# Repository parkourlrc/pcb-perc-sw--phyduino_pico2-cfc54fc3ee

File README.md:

# Phyduino Pico 2

An Arduino Uno-style development board built around the Raspberry Pi **RP2350** microcontroller, designed by the University of Toronto Department of Physics, Electronics Support Services, for the [Introduction to Electronics](https://perc-sw.github.io/intro_to_electronics/) course. Students assemble part of the board themselves, learning surface-mount soldering, microcontroller programming, analogue-to-digital conversion and digital communication.

**Project site:** <https://perc-sw.github.io/phyduino_pico2> (schematic, interactive BOM, PCB drawings, 3D model and datasheets)

> **Status:** Rev A0 prototype (October 2026).

## Features

### Microcontroller and memory
- **RP2350B** (QFN-80): dual Arm Cortex-M33 or Hazard3 RISC-V cores, 12 MHz crystal
- **16 MB** QSPI NOR flash (AT25QF128A)
- **8 MB** QSPI PSRAM (IS66WVS8M8FBLL)
- **8 KB** I²C EEPROM (AT24C64D)

### Analogue inputs
- Six analogue inputs (**A0–A5**) measured by an 8-channel, **12-bit SAR ADC** (ADS7038) on SPI
- The ADC runs from a dedicated 5 V analogue supply, with an **AREF** pin on the header
- The board's input voltage is monitored by one of the RP2350's own ADC inputs

### Wireless
- **ESP32-C6-MINI-1** module: 2.4 GHz Wi-Fi 6 and Bluetooth 5 (LE). The pin-compatible ESP32-C61-MINI-1 can be fitted instead.
- Runs [ESP-AT](https://github.com/perc-sw/esp-at) firmware as a network co-processor, connected to the RP2350 over UART with RTS/CTS flow control
- The RP2350 controls the module's enable and boot pins, and a separate UART is provided for loading the module's firmware

### Connectors and I/O
- **Arduino Uno R3 form factor** (68.6 × 53.3 mm) with standard headers: D0–D15, A0–A5, AREF, IOREF, RESET, 3.3 V, 5 V and V<sub>IN</sub>
- **USB-C:** USB 2.0 and 5 V power, with ESD protection
- **Qwiic / STEMMA QT** connector (I²C on D14/D15, 3.3 V)
- **HSTX connector** (22-pin, 0.5 mm FFC): the RP2350's four high-speed differential HSTX lanes, plus I²C and two GPIO
- **SWD debug connector** (3-pin JST-SH, Raspberry Pi debug probe pinout)
- **I²C GPIO expander** (FXL6408) for power-path status and control

### Power
- Two inputs:
  - **USB-C:** 4.5–5.5 V, up to 3 A
  - **DC barrel jack** (2.1 mm): 4.5–22 V, up to 3 A
- Each input has a **TPS25947 eFuse** with over-voltage, under-voltage and reverse-current protection and current limiting (2.6 A)
- **AP63301** synchronous buck regulators (3 A) generate the 3.3 V and 5 V rails
- A **TPS2121** power mux supplies the 5 V rail:
  - from the 5 V regulator when the input is above 5.5 V
  - directly from the input otherwise, for example on USB power

### Reset and boot
- One **RESET/BOOT** button, handled by a TPS3424 push-button controller:
  - **Short press:** reset and run the program in flash
  - **Long press (about 2 s):** restart in **UF2 (BOOTSEL) mode**, where the board appears as a USB drive for drag-and-drop programming

## Repository layout

| Path | Contents |
|---|---|
| `phyduino_pico2.kicad_pro` | KiCad project (net classes, design rules, DRC exclusions) |
| `phyduino_pico2.kicad_sch` | Root schematic: headers and connectors, with the Microcontroller, Power and Wireless Communication sub-sheets |
| `phyduino_pico2_mcu.kicad_sch` | Microcontroller: RP2350, crystal and debug connector, with two sub-sheets |
| `phyduino_pico_memory.kicad_sch` | Memory: QSPI flash, PSRAM and the RESET/BOOT button controller |
| `phyduino_pico_peripherals.kicad_sch` | Peripherals: ADC, EEPROM and I²C GPIO expander |
| `phyduino2_power_regs.kicad_sch` | Power: eFuses, power mux and buck regulators |
| `phyduino_pico2_wifi.kicad_sch` | Wireless Communication: ESP32-C6 module |
| `phyduino_pico2.kicad_pcb` | 4-layer PCB |
| `scripts/` | Pre-release check: documentation links, generated outputs, part numbers and pinout against the design |
| `ibom.config.ini` | Settings for the student interactive BOM (InteractiveHtmlBom plugin) |
| `fabrication/` | Gerber and drill files |
| `docs/` | [Project site](https://perc-sw.github.io/phyduino_pico2): schematic and PCB PDFs, interactive BOMs, 3D models, datasheets and design reviews |

## Opening the design

The design files are in **KiCad 10** format and can't be opened with earlier versions.

Some symbols and footprints come from the maintainer's own libraries, which aren't in this repository. KiCad may report these as missing library links. The board and schematic still open and plot correctly, because every footprint and symbol is stored in the design files.

The board's silkscreen and copper text use Liberation Sans, Tekton, Centaur and Photograph Signature. Install the fonts in [`.github/workflows/fonts/`](.github/workflows/fonts/) so the text renders as it does on the fabricated board.

## Related projects

- [Phyduino Pico](https://perc-sw.github.io/phyduino_pico/): the previous RP2040 board
- [Analog Shield](https://perc-sw.github.io/analog_shield)
- [Analog Shield 2](https://github.com/perc-sw/analog_shield2)
- [Phyduino Board Support](https://perc-sw.github.io/phyduino_bsp/) 

## Licence

Released under the GNU General Public License v3.0. See [LICENSE](LICENSE).

University of Toronto, Department of Physics: [Electronics Support Services](https://www.physics.utoronto.ca/physics-at-uoft/services/plrs/electronic-support-services/)

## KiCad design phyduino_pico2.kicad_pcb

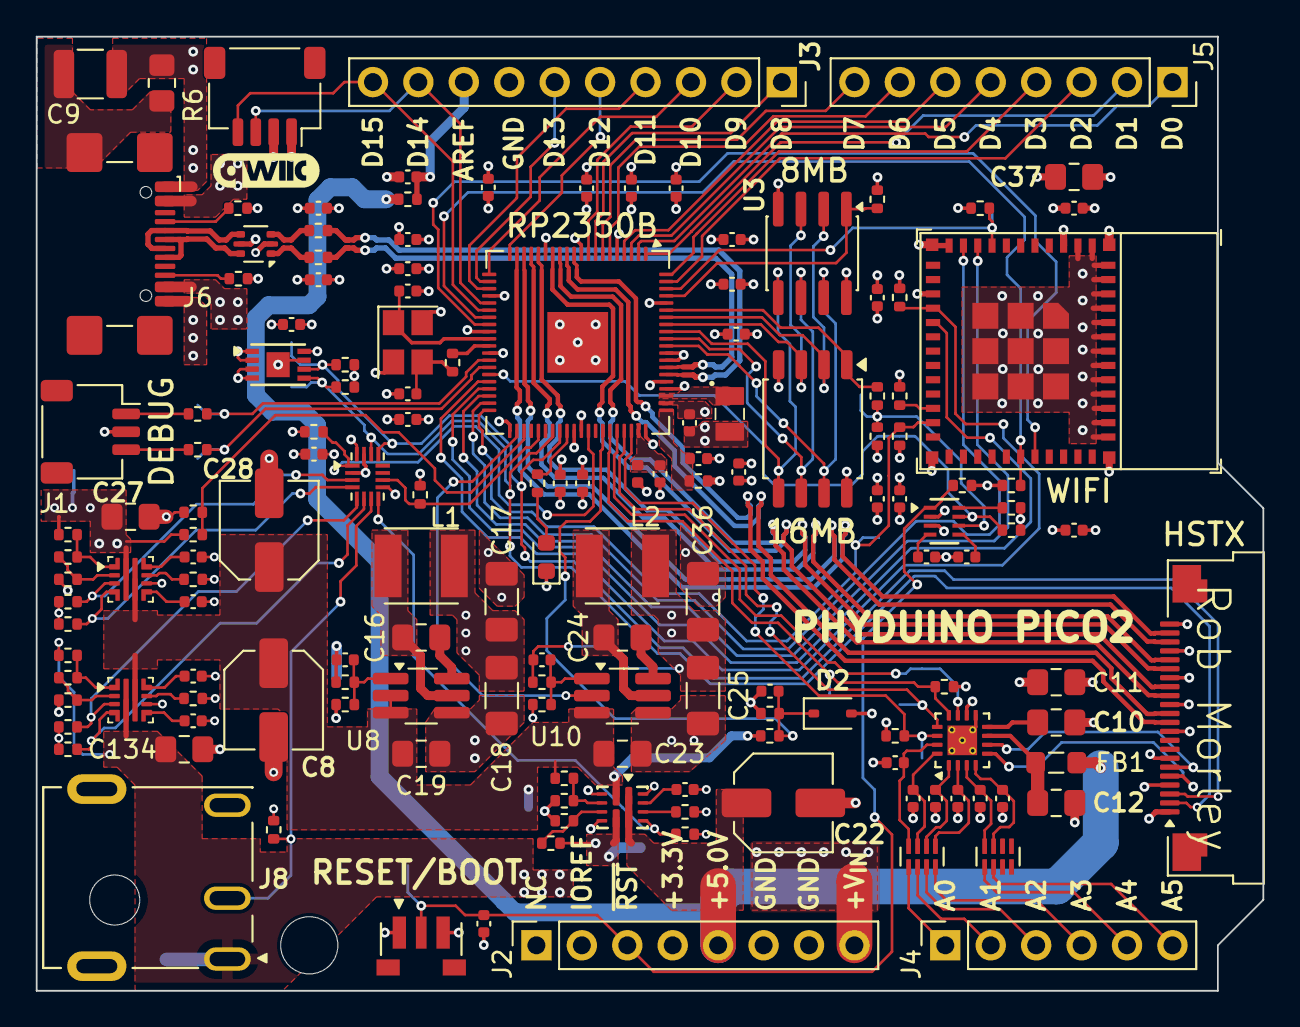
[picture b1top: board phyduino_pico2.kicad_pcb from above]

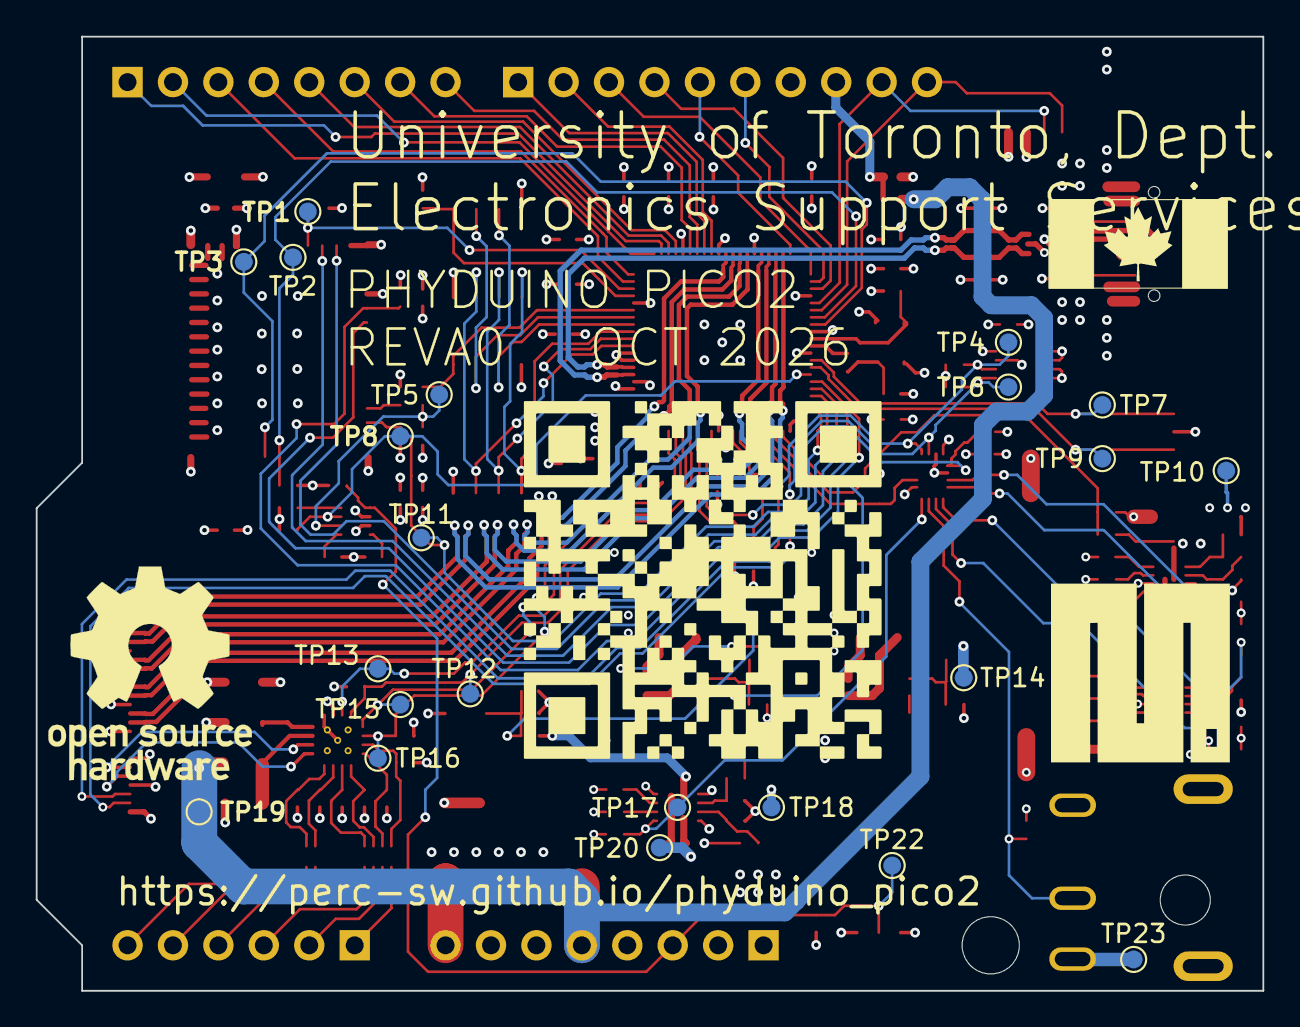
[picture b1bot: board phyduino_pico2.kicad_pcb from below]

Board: 4 copper layers, 68.6 x 53.3 mm, 175 parts (22 on the bottom side), 129 nets.

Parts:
C1, C6, C13, C20, C21, C26, C29, C34, C57, C110, C111, C117, C119, C125, C126, C127, C128, C129, C130, C131, C132, C133, C135, C137, C139: 0.1µF; C_0402_1005Metric
C2, C3, C4, C120: 4.7µF; C_0402_1005Metric
C5, C7: 100pF; C_0402_1005Metric
C8, C22, C28: 100µF; C_Elec_5x5.4
C9: 0.1µF; C_1210_3225Metric
C10, C11, C12, C134: 1µF; C_0805_2012Metric_Pad1.18x1.45mm_HandSolder
C14, C15: 27pF; C_0402_1005Metric
C16, C24: 0.1µF; C_0805_2012Metric_Pad1.18x1.45mm_HandSolder
C17, C18, C25, C36: 22µF; C_1206_3216Metric_Pad1.33x1.80mm_HandSolder
C19, C23, C27, C37: 10µF; C_0805_2012Metric_Pad1.18x1.45mm_HandSolder
C30, C31, C32, C33, C35, C38, C59: 1000pF; C_0402_1005Metric
C39: 1µF; C_0402_1005Metric
C58: 4700pF; C_0402_1005Metric
C136, C141: 1nF; C_0402_1005Metric
C140: 3300pF; C_0402_1005Metric
D1: GREEN; LED_0603_1608Metric
D2: 3.6V; D_SOD-323
FB1: 1kΩ@100MHz; L_0805_2012Metric_Pad1.05x1.20mm_HandSolder
FB100: MPZ1005S221HT000; L_0402_1005Metric
H2: MountingHole; MountingHole_3.2mm_M3
J1: SM03B-SRSS-TB; JST_SH_SM03B-SRSS-TB_1x03-1MP_P1.00mm_Horizontal
J2, J5: PPPC081LFBN-RC; PinSocket_1x08_P2.54mm_Vertical
J3: PPPC101LFBN-RC; PinSocket_1x10_P2.54mm_Vertical
J4: PPPC061LFBN-RC; PinSocket_1x06_P2.54mm_Vertical
J6: USB4110-GF-A; GCT-USBC-GCT_USB4110
J7: F32Q-1A7H1-11022; Amphenol_F32Q-1A7x1-11022_1x22-1MP_P0.5mm_Horizontal
J8: 54-00127; TENSILITY_54-00127
J9: SM04B-SRSS-TB; JST_SH_SM04B-SRSS-TB_1x04-1MP_P1.00mm_Horizontal
L1: 6.8µH; L_Bourns_SRP4021HMCT
L2: 10µH; L_Bourns_SRP4021HMCT
L3: 3.3µH; L_Abracon_AOTA-B201610S
R1, R2: 100Ω; R_0402_1005Metric
R3, R4, R5: 27Ω; R_0402_1005Metric
R6: 220kΩ; R_0805_2012Metric_Pad1.20x1.40mm_HandSolder
R13: 620Ω; R_0402_1005Metric
R20, R21, R22, R44, R45, R49, R51, R52, R53, R63, R64, R136, R137, R153, R157, R158, R162, R163, R164, R166: 10kΩ; R_0402_1005Metric
R42, R43, R47, R48, R50, R55, R61, R62, R65: 5.1kΩ; R_0402_1005Metric
R46, R139, R156: 1.1kΩ; R_0402_1005Metric
R56: 196kΩ; R_0402_1005Metric
R57: 62kΩ; R_0402_1005Metric
R58: 158kΩ; R_0402_1005Metric
R59: 30kΩ; R_0402_1005Metric
R134, R135, R138: 42.2kΩ; R_0402_1005Metric
R143, R149: 732kΩ; R_0402_1005Metric
R146, R155: 215kΩ; R_0402_1005Metric
R150, R154: 53.6kΩ; R_0402_1005Metric
R151: 22kΩ; R_0402_1005Metric
R152: 33kΩ; R_0402_1005Metric
R165: 100kΩ; R_0402_1005Metric
RN1, RN2: 1.0kΩ; RESCAV50P200X100X55-8N
SW1: 1977067-1; TE_1977067-1
TP1, TP2, TP3, TP4, TP5, TP6, TP7, TP8, TP9, TP10, TP11, TP12, TP13, TP14, TP15, TP16, TP17, TP18, TP19, TP20, TP22, TP23: TestPoint_Small; TestPoint_SameSky_CPG-47-TH-B
U1: RP2350B; QFN-80-1EP_10x10mm_P0.4mm_EP3.4x3.4mm
U2: AT25QF128A-SHB-T; SOIC-8_5.3x5.3mm_P1.27mm
U3: IS66WVS8M8FBLL-104NLI; SOIC-8_3.9x4.9mm_P1.27mm
U5: ADS7038IRTER; QFN50P300X300X80-17N
U6, U13: TPS259470ARPWR; Texas_Instruments_VQFN-HR-10
U7: AT24C64D-MAHM-T; DFN-8-1EP_3x2mm_P0.5mm_EP1.3x1.4mm
U8, U10: AP63301WU-7; TSOT-23-6_HandSoldering
U9: USBLC6-2P6; SOT-666
U11: ESP32-C6-MINI-1-H4; ESP32-C6-MINI-1
U14: FXL6408UMX; QFN40P260X180X55-16N
U15: TPS3424C11EF2ADRLR; SOT-5x3_DRL0008A_TEX
U108: TPS2121RUXR; VQFN-HR-12
Y1: ABM8G-12.000MHZ-18-D2Y-T; Crystal_SMD_Abracon_ABM8AIG-4Pin_3.2x2.5mm

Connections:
+1.1V: C2.1, C119.1, C120.1, C135.1, L3.1, U1.10 (DVDD), U1.32 (DVDD), U1.51 (DVDD), U1.65 (VREG_FB)
+3.3V: C1.1, C3.1, C5.1, C6.1, C11.1, C13.1, C17.1, C18.1, C20.1, C21.1, C26.1, C29.1, C34.1, C37.2, C110.1, C111.1, C125.1, C126.1, C127.1, C128.1, C129.1, C130.1, C133.1, C137.1, FB100.1, J2.2, J2.4, J7.1, J9.2, L1.2, R5.1, R20.1, R21.1, R22.1, R42.1, R43.1, R44.1, R45.1, R50.1, R51.1, R52.2, R55.1, R56.1, R61.1, R62.1, R63.1, R64.1, R153.2, R157.2, R158.2, R162.2, R163.2, R164.2, TP14.1 (1_1), U1.5 (IOVDD), U1.15 (IOVDD), U1.24 (IOVDD), U1.29 (IOVDD), U1.41 (IOVDD), U1.50 (IOVDD), U1.60 (IOVDD), U1.64 (VREG_VIN), U1.68 (USB_OTP_VDD), U1.69 (QSPI_IOVDD), U1.76 (IOVDD), U2.8 (VCC), U3.8 (VDD), U5.10 (DVDD), U7.8 (VCC), U9.5 (VBUS), U11.3 (3V3), U14.2 (VDDIO), U14.15 (VCC), U15.3 (VDD)
+3.3VA: C117.1, FB100.2, U1.59 (ADC_AVDD)
+5.0V: C22.1, FB1.1, J2.5, R65.1, TP19.1 (1_1), U108.1 (OUT), U108.8 (OUT)
+5.0VA: C12.1, FB1.2, U5.7 (AVDD)
+5.0V_DCDC: C7.1, C25.1, C36.1, L2.2, R58.1, R135.2, TP20.1 (1_1), U108.7 (IN1)
+VIN_REG: C8.1, C19.1, C23.1, C28.1, R138.2, R165.2, TP18.1 (1_1), U6.6 (OUT), U8.2 (EN), U8.3 (IN), U10.3 (IN), U13.6 (OUT), U108.2 (IN2)
+V_{EXTERNAL}: C134.1, J2.8, J8.1, R143.2, TP23.1 (1_1), U6.5 (IN)
+V_{USB}: C27.1, J6.A4 (VBUS), J6.A9 (VBUS), J6.B4 (VBUS), J6.B9 (VBUS), R149.2, R151.2, TP10.1 (1_1), U13.5 (IN)
/AREF: C39.1, J3.8, R65.2
/Microcontroller/A0: J4.1, RN1.1 (R1.1)
/Microcontroller/A1: J4.2, RN1.2 (R2.1)
/Microcontroller/A2: J4.3, RN1.3 (R3.1)
/Microcontroller/A3: J4.4, RN1.4 (R4.1)
/Microcontroller/A4: J4.5, RN2.1 (R1.1)
/Microcontroller/A5: J4.6, RN2.2 (R2.1)
/Microcontroller/ADC_MISO: R43.2, TP12.1 (1_1), U1.55 (GPIO44), U5.12 (SDO)
/Microcontroller/ADC_MOSI: R42.2, TP16.1 (1_1), U1.58 (GPIO47), U5.14 (SDI)
/Microcontroller/ADC_SCK: TP15.1 (1_1), U1.57 (GPIO46), U5.13 (SCLK)
/Microcontroller/ADC_nCS: TP13.1 (1_1), U1.56 (GPIO45), U5.11 (~CS)
/Microcontroller/BUILTIN_LED: R46.1, U1.49 (GPIO40)
/Microcontroller/D0: J5.1, U1.2 (GPIO5)
/Microcontroller/D1: J5.2, U1.1 (GPIO4)
/Microcontroller/D2: J5.3, U1.79 (GPIO2)
/Microcontroller/D3: J5.4, U1.80 (GPIO3)
/Microcontroller/D4: J5.5, U1.3 (GPIO6)
/Microcontroller/D5: J5.6, U1.4 (GPIO7)
/Microcontroller/D6: J5.7, U1.6 (GPIO8)
/Microcontroller/D7: J5.8, U1.7 (GPIO9)
/Microcontroller/D8: J3.1, U1.8 (GPIO10)
/Microcontroller/D9: J3.2, U1.9 (GPIO11)
/Microcontroller/D10: J3.3, U1.21 (GPIO21)
/Microcontroller/D11: J3.4, U1.23 (GPIO23)
/Microcontroller/D12: J3.5, U1.20 (GPIO20)
/Microcontroller/D13: J3.6, U1.22 (GPIO22)
/Microcontroller/D14: J3.9, J9.3, U1.25 (GPIO24)
/Microcontroller/D15: J3.10, J9.4, U1.26 (GPIO25)
/Microcontroller/DBIO_SWCLK: R1.2, TP7.1 (1_1), U1.33 (SWCLK)
/Microcontroller/DBIO_SWDIO: R2.2, TP9.1 (1_1), U1.34 (SWDIO)
/Microcontroller/DEBUG_SWCLK: J1.1, R1.1
/Microcontroller/DEBUG_SWDIO: J1.3, R2.1
/Microcontroller/EN_5V: U1.42 (GPIO33), U10.2 (EN)
/Microcontroller/EXT_AUXOFF: R158.1, U6.3 (AUXOFF), U14.5 (GPIO5)
/Microcontroller/EXT_~FLT: R157.1, U6.4 (~FLT), U14.6 (GPIO4)
/Microcontroller/EXT_~RESET: C57.1, J2.3, R22.2, SW1.2, TP22.1 (1_1), U15.1 (PB)
/Microcontroller/FLASH_CLK: U1.71 (QSPI_SCK), U2.6 (SCK), U3.6 (CLK)
/Microcontroller/FLASH_SD0: U1.72 (QSPI_SD0), U2.5 (I/O_{0}), U3.5 (SIO0)
/Microcontroller/FLASH_SD1: U1.74 (QSPI_SD1), U2.2 (I/O_{1}), U3.2 (SIO1)
/Microcontroller/FLASH_SD2: U1.73 (QSPI_SD2), U2.3 (IO_{2}), U3.3 (SIO2)
/Microcontroller/FLASH_SD3: U1.70 (QSPI_SD3), U2.7 (I/O_{3}), U3.7 (SIO3)
/Microcontroller/FLASH_~CS: R49.1, U1.75 (QSPI_~CS), U2.1 (~CS)
/Microcontroller/HSTX_LANE0_N: J7.12, U1.12 (GPIO13)
/Microcontroller/HSTX_LANE0_P: J7.11, U1.11 (GPIO12)
/Microcontroller/HSTX_LANE1_N: J7.15, U1.14 (GPIO15)
/Microcontroller/HSTX_LANE1_P: J7.14, U1.13 (GPIO14)
/Microcontroller/HSTX_LANE2_N: J7.18, U1.17 (GPIO17)
/Microcontroller/HSTX_LANE2_P: J7.17, U1.16 (GPIO16)
/Microcontroller/HSTX_LANE3_N: J7.21, U1.19 (GPIO19)
/Microcontroller/HSTX_LANE3_P: J7.20, U1.18 (GPIO18)
/Microcontroller/HS_GPIO0: J7.5, U5.5 (AIN6/GPIO6)
/Microcontroller/HS_GPIO1: J7.6, U5.6 (AIN7/GPIO7)
/Microcontroller/I2C1_SCL: J7.3, R62.2, TP4.1 (1_1), U1.48 (GPIO39), U7.6 (SCL), U14.13 (SCL)
/Microcontroller/I2C1_SDA: J7.2, R61.2, TP6.1 (1_1), U1.47 (GPIO38), U7.5 (SDA), U14.14 (SDA)
/Microcontroller/IO_EXP_~INT: R63.2, U1.52 (GPIO41), U14.1 (~INT)
/Microcontroller/IO_EXP_~RST: R64.2, U1.45 (GPIO36), U14.10 (~RST)
/Microcontroller/MCU_VREG_AVDD: C4.1, R5.2, U1.61 (VREG_AVDD)
/Microcontroller/MCU_VREG_LX: L3.2, U1.63 (VREG_LX)
/Microcontroller/MCU_XIN: C14.1, U1.30 (XIN), Y1.1
/Microcontroller/MCU_XOUT: R13.2, U1.31 (XOUT)
/Microcontroller/Memory/BOOT_LP_CAP: C58.1, U15.5 (LPT)
/Microcontroller/Memory/MCU_BOOT_SEL: R49.2, R52.1, TP5.1 (1_1), U15.6 (~RESET)
/Microcontroller/Memory/RESET_SP_CAP: C59.1, U15.4 (SPT)
/Microcontroller/PSW_STATUS: R153.1, TP17.1 (1_1), U14.8 (GPIO2), U108.9 (ST)
/Microcontroller/Peripherals/AIN0: C30.1, RN1.8 (R1.2), U5.15 (AIN0/GPIO0)
/Microcontroller/Peripherals/AIN1: C31.1, RN1.7 (R2.2), U5.16 (AIN1/GPIO1)
/Microcontroller/Peripherals/AIN2: C32.1, RN1.6 (R3.2), U5.1 (AIN2/GPIO2)
/Microcontroller/Peripherals/AIN3: C33.1, RN1.5 (R4.2), U5.2 (AIN3/GPIO3)
/Microcontroller/Peripherals/AIN4: C35.1, RN2.8 (R1.2), U5.3 (AIN4/GPIO4)
/Microcontroller/Peripherals/AIN5: C38.1, RN2.7 (R2.2), U5.4 (AIN5/GPIO5)
/Microcontroller/SYS_nRST: R20.2, TP8.1 (1_1), U1.35 (RUN), U15.7 (~INT)
/Microcontroller/USB_AUXOFF: R163.1, U13.3 (AUXOFF), U14.3 (GPIO7)
/Microcontroller/USB_D_N: R3.1, U9.3 (I/O2)
/Microcontroller/USB_D_P: R4.1, U9.1 (I/O1)
/Microcontroller/USB_IO_D_N: R3.2, U1.66 (USB_DM)
/Microcontroller/USB_IO_D_P: R4.2, U1.67 (USB_DP)
/Microcontroller/USB_~FLT: R162.1, U13.4 (~FLT), U14.4 (GPIO6)
/Microcontroller/VBUS_DETECT: R151.1, R152.2, U1.43 (GPIO34)
/Microcontroller/VIN_MONITOR: C141.1, D2.1 (K), R165.1, R166.2, U1.54 (GPIO43)
/Microcontroller/WIFI_BOOT1: R44.2, TP11.1 (1_1), U1.40 (GPIO32), U11.23 (IO9)
/Microcontroller/WIFI_DL_UART_RX: TP3.1 (1_1), U1.28 (GPIO27), U11.31 (TXD0)
/Microcontroller/WIFI_DL_UART_TX: R50.2, TP2.1 (1_1), U1.27 (GPIO26), U11.30 (RXD0)
/Microcontroller/WIFI_ENA: R53.1, TP1.1 (1_1), U1.78 (GPIO1), U11.8 (EN)
/Microcontroller/WIFI_UART_CTS: U1.38 (GPIO30), U11.9 (IO4)
/Microcontroller/WIFI_UART_RTS: U1.39 (GPIO31), U11.10 (IO5)
/Microcontroller/WIFI_UART_RX: U1.37 (GPIO29), U11.16 (IO7)
/Microcontroller/WIFI_UART_TX: R55.2, U1.36 (GPIO28), U11.15 (IO6)
/Microcontroller/XOUT: C15.1, R13.1, Y1.3
/Microcontroller/~EXT_PWR: J8.3, R164.1, U14.7 (GPIO3)
/Power/DCDC_3V3_BST: C16.1, U8.6 (BST)
/Power/DCDC_3V3_FB: C5.2, R56.2, R57.1, U8.1 (FB)
/Power/DCDC_3V3_SW: C16.2, L1.1, U8.5 (SW)
/Power/DCDC_5V0_BST: C24.1, U10.6 (BST)
/Power/DCDC_5V0_FB: C7.2, R58.2, R59.1, U10.1 (FB)
/Power/DCDC_5V0_SW: C24.2, L2.1, U10.5 (SW)
/Power/EXT_ILIM: R139.2, U6.9 (ILM)
/Power/EXT_ITIMER: C132.1, U6.10 (ITIMER)
/Power/EXT_OVLO: R146.1, R150.2, U6.2 (OVLO)
/Power/EXT_UVLO: R143.1, R146.2, U6.1 (EN/UVLO)
/Power/EXT_dVdt: C136.1, U6.7 (dVdt)
/Power/PMUX_LIM: R134.2, U108.10 (ILM)
/Power/PMUX_OV1: R135.1, R136.2, U108.5 (OV1)
/Power/PMUX_OV2: R137.2, R138.1, U108.4 (OV2)
/Power/PMUX_SS: C131.1, U108.11 (SS)
/Power/USB_ILIM: R156.2, U13.9 (ILM)
/Power/USB_ITIMER: C139.1, U13.10 (ITIMER)
/Power/USB_OVLO: R154.1, R155.2, U13.2 (OVLO)
/Power/USB_UVLO: R149.1, R154.2, U13.1 (EN/UVLO)
/Power/USB_dVdt: C140.1, U13.7 (dVdt)
/USB_CC1: J6.A5 (CC1), R48.1
/USB_CC2: J6.B5 (CC2), R47.1
/USB_COM_D_N: J6.A7 (D-), J6.B7 (D-), U9.4 (I/O2)
/USB_COM_D_P: J6.A6 (D+), J6.B6 (D+), U9.6 (I/O1)
/USB_COM_SHIELD: C9.1, J6.S2 (SH), R6.1
/Wireless Communication/WIFI_BOOT0: R45.2, U11.22 (IO8)
GND: C1.2, C2.2, C3.2, C4.2, C6.2, C8.2, C9.2, C10.2, C11.2, C12.2, C13.2, C14.2, C15.2, C17.2, C18.2, C19.2, C20.2, C21.2, C22.2, C23.2, C25.2, C26.2, C27.2, C28.2, C29.2, C30.2, C31.2, C32.2, C33.2, C34.2, C35.2, C36.2, C37.1, C38.2, C39.2, C57.2, C58.2, C59.2, C110.2, C111.2, C117.2, C119.2, C120.2, C125.2, C126.2, C127.2, C128.2, C129.2, C130.2, C131.2, C132.2, C133.2, C134.2, C135.2, C136.2, C137.2, C139.2, C140.2, C141.2, D1.1 (K), D2.2 (A), J1.2, J2.6, J2.7, J3.7, J6.A1 (GND), J6.A12 (GND), J6.B1 (GND), J6.B12 (GND), J7.4, J7.7, J7.10, J7.13, J7.16, J7.19, J7.22, J8.2, J9.1, R6.2, R47.2, R48.2, R53.2, R57.2, R59.2, R134.1, R136.1, R137.1, R139.1, R150.1, R152.1, R155.1, R156.1, R166.1, SW1.1, SW1.3 (1), U1.62 (VREG_PGND), U1.81 (GND), U2.4 (GND), U3.4 (VSS), U5.9 (GND), U5.17 (PAD), U6.8 (GND), U7.1 (A0), U7.2 (A1), U7.3 (A2), U7.4 (VSS), U7.7 (WP), U7.9 (EP), U8.4 (GND), U9.2 (GND), U10.4 (GND), U11.1 (GND), U11.2 (GND), U11.11 (GND), U11.14 (GND), U11.36 (GND), U11.37 (GND), U11.38 (GND), U11.39 (GND), U11.40 (GND), U11.41 (GND), U11.42 (GND), U11.43 (GND), U11.44 (GND), U11.45 (GND), U11.46 (GND), U11.47 (GND), U11.48 (GND), U11.49 (GND), U11.50 (GND), U11.51 (GND), U11.52 (GND), U11.53 (GND), U13.8 (GND), U14.9 (ADDR), U14.16 (GND), U15.2 (GND), U108.3 (CP2), U108.6 (PR1), U108.12 (GND), Y1.2, Y1.4
unnamed: D1.2 (A), R46.2
unnamed: C10.1, U5.8 (DECAP)
unnamed: R21.2, U15.8 (KILL)
PSRAM_CE#: R51.2, U1.77 (GPIO0), U3.1 (CE#)

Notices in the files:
README.md:
Licence: GPL v3
